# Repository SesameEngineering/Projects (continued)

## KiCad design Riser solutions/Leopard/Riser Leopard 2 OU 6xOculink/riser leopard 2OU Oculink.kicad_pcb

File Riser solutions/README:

In this folder you can find the different OCP riser solutions for both Leopard servers and Tioga Pass

For each you can find a quick summary on how to use them, electrical files (design and production files) and mechanical files for the bracket when needed

Electrical design has been done with Kicad

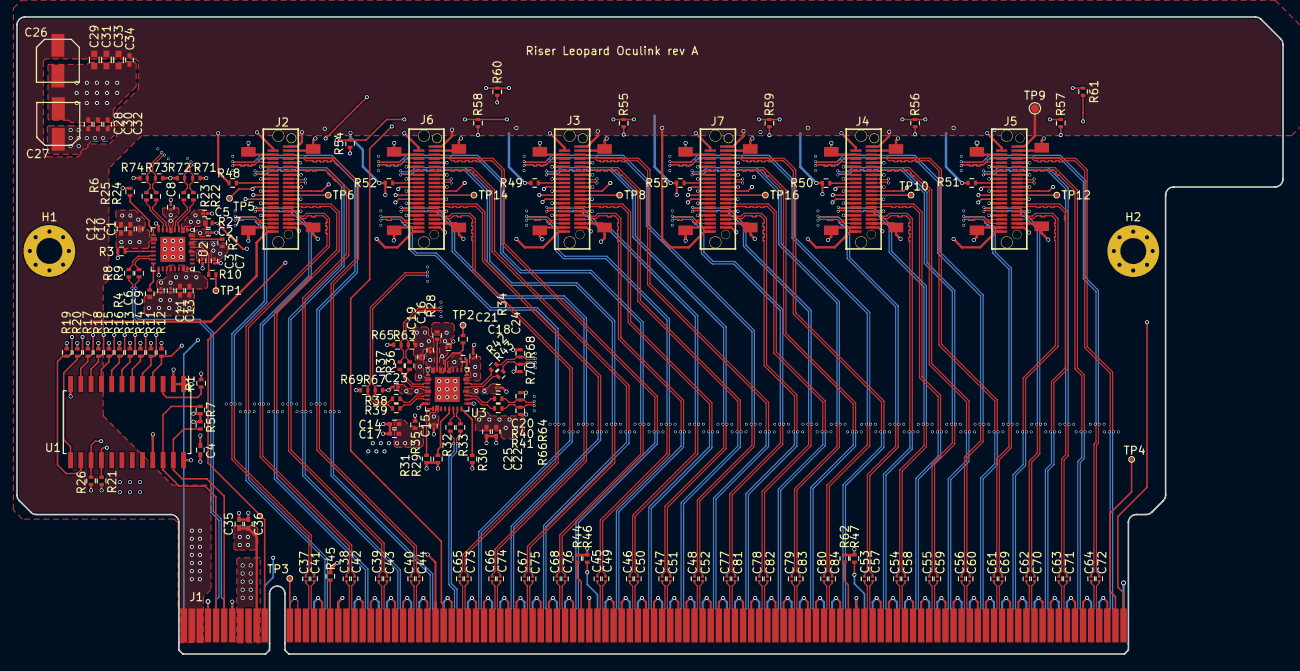
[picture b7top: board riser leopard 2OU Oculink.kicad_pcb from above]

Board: 6 copper layers, 156.4 x 78.7 mm, 183 parts (1 on the bottom side), 238 nets.

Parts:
C1, C2, C3, C5, C6, C7, C8, C9, C15, C16, C18, C19, C20, C21, C23, C24: 0.01u; C_0201
C4, C12, C13, C17, C25, C28, C30, C35: 1u 10V; C_0402
C10, C11, C14, C22: 10u 10V; C_0402
C26, C27: 100u 16V; CapaElec_100u_16V_5.3x5.3mm
C29, C31, C33: 1u 25V; C_0603
C32, C36: 0.1u 10V; C_0402
C34: 0.1u 25V; C_0402
C37, C38, C39, C40, C41, C42, C43, C44, C45, C46, C47, C48, C49, C50, C51, C52, C53, C54, C55, C56, C57, C58, C59, C60, C61, C62, C63, C64, C65, C66, C67, C68, C69, C70, C71, C72, C73, C74, C75, C76, C77, C78, C79, C80, C81, C82, C83, C84: 0.22u; C_0201
H1, H2: MountingHole_Pad; MountingHole_3.2mm_M3_Pad_Via
J1: CONN_PCIE_x24; pads_pcie_x24
J2, J3, J4, J5, J6, J7: Oculink_x4; Oculink_x4_straight_G14A42221612AHR
R1, R5, R7, R11, R12, R13, R14, R15, R16, R17, R18, R19, R20, R21, R26, R44, R45, R48, R49, R50, R51, R52, R53: 4.7k; R_0402
R2, R3, R4, R6, R28, R29, R30, R31: 2.2k; R_0402
R8, R9, R10, R22, R23, R24, R25, R27, R32, R33, R34, R35, R36, R37, R38, R39, R40, R41, R42, R43, R46, R47, R54, R55, R56, R57, R58, R59, R60, R61, R62: 0; R_0402
R63, R64, R65, R66, R67, R68, R69, R70, R71, R72, R73, R74: 49.9; R_0402
TP1, TP2: REFout; TestPoint_Pad_D0.5mm
TP3: LAN_SMB_ALERT_N; TestPoint_Pad_D0.5mm
TP4: TP1; TestPoint_Pad_D0.5mm
TP5: TP2; TestPoint_Pad_D0.5mm
TP6, TP8, TP10, TP12, TP14, TP16: BP_TYPE; TestPoint_Pad_D0.5mm
TP7: 3.3V; TestPoint_Pad_D1.0mm
TP9: 12V; TestPoint_Pad_D1.0mm
U1: PCA9548ADW; SOIC-24W_7.5x15.4mm_Pitch1.27mm
U2, U3: CLK_Buffer_4output_LMK00334RTVTQ1; WQFN-32-1EP_5x5mm_Pitch0.5mm

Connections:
+3.3VP: C5.2, C6.2, C7.2, C8.2, C9.2, C11.1, C13.1, C19.2, C20.2, C21.2, C22.1, C23.2, C24.2, C25.1, R2.2, R27.1, R28.2, R35.1, U2.2, U2.5, U2.20, U2.23, U2.30, U3.2, U3.5, U3.20, U3.23, U3.30
+3.3Vaux: C4.1, C35.1, C36.1, J1.B10, R1.2, R5.2, R7.2, R11.2, R12.2, R13.2, R14.2, R15.2, R16.2, R17.2, R18.2, R19.2, R20.2, R21.2, R26.2, U1.24
+3V3: C1.1, C2.1, C3.1, C10.1, C12.1, C14.1, C15.1, C16.1, C17.1, C18.1, C27.1, C28.1, C30.1, C32.1, J1.A9, J1.A10, J1.B8, J2.A1, J2.B21, J3.A1, J3.B21, J4.A1, J4.B21, J5.A1, J5.B21, J6.A1, J6.B21, J7.A1, J7.B21, R27.2, R35.2, R48.2, R49.2, R50.2, R51.2, R52.2, R53.2, TP7.1, U2.10, U2.28, U2.32, U3.10, U3.28, U3.32
+12V: C26.1, C29.1, C31.1, C33.1, C34.1, J1.A2, J1.A3, J1.B1, J1.B2, J1.B3, J2.A21, J2.B1, J3.A21, J3.B1, J4.A21, J4.B1, J5.A21, J5.B1, J6.A21, J6.B1, J7.A21, J7.B1, TP9.1
/CLK and I2C buffer/CLK100_R_SLOT0+: R8.2, U2.14
/CLK and I2C buffer/CLK100_R_SLOT0-: R9.2, U2.15
/CLK and I2C buffer/CLK100_R_SLOT1+: R32.2, U3.14
/CLK and I2C buffer/CLK100_R_SLOT1-: R33.2, U3.15
/CLK and I2C buffer/Oculink_0_R_CLK100+: R22.2, U2.3
/CLK and I2C buffer/Oculink_0_R_CLK100-: R23.2, U2.4
/CLK and I2C buffer/Oculink_1_R_CLK100+: R24.2, U2.6
/CLK and I2C buffer/Oculink_1_R_CLK100-: R25.2, U2.7
/CLK and I2C buffer/Oculink_2_R_CLK100+: R38.2, U3.6
/CLK and I2C buffer/Oculink_2_R_CLK100-: R39.2, U3.7
/CLK and I2C buffer/Oculink_3_R_CLK100+: R36.2, U3.3
/CLK and I2C buffer/Oculink_3_R_CLK100-: R37.2, U3.4
/CLK and I2C buffer/Oculink_4_R_CLK100+: R42.2, U3.22
/CLK and I2C buffer/Oculink_4_R_CLK100-: R43.2, U3.21
/CLK and I2C buffer/Oculink_5_R_CLK100+: R40.2, U3.19
/CLK and I2C buffer/Oculink_5_R_CLK100-: R41.2, U3.18
/Oculink connectors/Oculink_0_C_x4_TX0+: C37.2, J2.B3
/Oculink connectors/Oculink_0_C_x4_TX0-: C41.2, J2.B4
/Oculink connectors/Oculink_0_C_x4_TX1+: C38.2, J2.B6
/Oculink connectors/Oculink_0_C_x4_TX1-: C42.2, J2.B7
/Oculink connectors/Oculink_0_C_x4_TX2+: C39.2, J2.B15
/Oculink connectors/Oculink_0_C_x4_TX2-: C43.2, J2.B16
/Oculink connectors/Oculink_0_C_x4_TX3+: C40.2, J2.B18
/Oculink connectors/Oculink_0_C_x4_TX3-: C44.2, J2.B19
/Oculink connectors/Oculink_1_C_x4_TX0+: C65.2, J6.B3
/Oculink connectors/Oculink_1_C_x4_TX0-: C73.2, J6.B4
/Oculink connectors/Oculink_1_C_x4_TX1+: C66.2, J6.B6
/Oculink connectors/Oculink_1_C_x4_TX1-: C74.2, J6.B7
/Oculink connectors/Oculink_1_C_x4_TX2+: C67.2, J6.B15
/Oculink connectors/Oculink_1_C_x4_TX2-: C75.2, J6.B16
/Oculink connectors/Oculink_1_C_x4_TX3+: C68.2, J6.B18
/Oculink connectors/Oculink_1_C_x4_TX3-: C76.2, J6.B19
/Oculink connectors/Oculink_2_C_x4_TX0+: C45.2, J3.B3
/Oculink connectors/Oculink_2_C_x4_TX0-: C49.2, J3.B4
/Oculink connectors/Oculink_2_C_x4_TX1+: C46.2, J3.B6
/Oculink connectors/Oculink_2_C_x4_TX1-: C50.2, J3.B7
/Oculink connectors/Oculink_2_C_x4_TX2+: C47.2, J3.B15
/Oculink connectors/Oculink_2_C_x4_TX2-: C51.2, J3.B16
/Oculink connectors/Oculink_2_C_x4_TX3+: C48.2, J3.B18
/Oculink connectors/Oculink_2_C_x4_TX3-: C52.2, J3.B19
/Oculink connectors/Oculink_3_C_x4_TX0+: C77.2, J7.B3
/Oculink connectors/Oculink_3_C_x4_TX0-: C81.2, J7.B4
/Oculink connectors/Oculink_3_C_x4_TX1+: C78.2, J7.B6
/Oculink connectors/Oculink_3_C_x4_TX1-: C82.2, J7.B7
/Oculink connectors/Oculink_3_C_x4_TX2+: C79.2, J7.B15
/Oculink connectors/Oculink_3_C_x4_TX2-: C83.2, J7.B16
/Oculink connectors/Oculink_3_C_x4_TX3+: C80.2, J7.B18
/Oculink connectors/Oculink_3_C_x4_TX3-: C84.2, J7.B19
/Oculink connectors/Oculink_4_C_x4_TX0+: C53.2, J4.B3
/Oculink connectors/Oculink_4_C_x4_TX0-: C57.2, J4.B4
/Oculink connectors/Oculink_4_C_x4_TX1+: C54.2, J4.B6
/Oculink connectors/Oculink_4_C_x4_TX1-: C58.2, J4.B7
/Oculink connectors/Oculink_4_C_x4_TX2+: C55.2, J4.B15
/Oculink connectors/Oculink_4_C_x4_TX2-: C59.2, J4.B16
/Oculink connectors/Oculink_4_C_x4_TX3+: C56.2, J4.B18
/Oculink connectors/Oculink_4_C_x4_TX3-: C60.2, J4.B19
/Oculink connectors/Oculink_5_C_x4_TX0+: C61.2, J5.B3
/Oculink connectors/Oculink_5_C_x4_TX0-: C69.2, J5.B4
/Oculink connectors/Oculink_5_C_x4_TX1+: C62.2, J5.B6
/Oculink connectors/Oculink_5_C_x4_TX1-: C70.2, J5.B7
/Oculink connectors/Oculink_5_C_x4_TX2+: C63.2, J5.B15
/Oculink connectors/Oculink_5_C_x4_TX2-: C71.2, J5.B16
/Oculink connectors/Oculink_5_C_x4_TX3+: C64.2, J5.B18
/Oculink connectors/Oculink_5_C_x4_TX3-: C72.2, J5.B19
/PCIe x24/PCIE_SLOT0_PRSNT_x4: J1.B17, R45.2
/PCIe x24/PCIE_SLOT1_PRSNT_x1x4: J1.B48, R44.2
/PCIe x24/PRSNT1#: J1.A1, R60.1, R61.1
/PCIe x24/SLOT0_CONFIG: J1.A50, R46.2
/PCIe x24/SLOT1_CONFIG: J1.A83, R47.2
CLK100_SLOT0+: J1.A5, R8.1
CLK100_SLOT0-: J1.A6, R9.1
CLK100_SLOT1+: J1.A32, R32.1
CLK100_SLOT1-: J1.A33, R33.1
GND: C1.2, C2.2, C3.2, C4.2, C5.1, C6.1, C7.1, C8.1, C9.1, C10.2, C11.2, C12.2, C13.2, C14.2, C15.2, C16.2, C17.2, C18.2, C19.1, C20.1, C21.1, C22.2, C23.1, C24.1, C25.2, C26.2, C27.2, C28.2, C29.2, C30.2, C31.2, C32.2, C33.2, C34.2, C35.2, C36.2, H1.1, H2.1, J1.A4, J1.A7, J1.A12, J1.A15, J1.A18, J1.A20, J1.A23, J1.A24, J1.A27, J1.A28, J1.A31, J1.A34, J1.A37, J1.A38, J1.A41, J1.A42, J1.A45, J1.A46, J1.A49, J1.A51, J1.A54, J1.A55, J1.A58, J1.A59, J1.A62, J1.A63, J1.A66, J1.A67, J1.A70, J1.A71, J1.A74, J1.A75, J1.A78, J1.A79, J1.A82, J1.A84, J1.A87, J1.A88, J1.A91, J1.A92, J1.A95, J1.A96, J1.A99, J1.A100, J1.A103, J1.A104, J1.A107, J1.A108, J1.A111, J1.A112, J1.A115, J1.B4, J1.B7, J1.B13, J1.B16, J1.B18, J1.B21, J1.B22, J1.B25, J1.B26, J1.B29, J1.B30, J1.B32, J1.B35, J1.B36, J1.B39, J1.B40, J1.B43, J1.B44, J1.B47, J1.B49, J1.B52, J1.B53, J1.B56, J1.B57, J1.B60, J1.B61, J1.B64, J1.B65, J1.B68, J1.B69, J1.B72, J1.B73, J1.B76, J1.B77, J1.B80, J1.B82, J1.B85, J1.B86, J1.B89, J1.B90, J1.B93, J1.B94, J1.B97, J1.B98, J1.B101, J1.B102, J1.B105, J1.B106, J1.B109, J1.B110, J1.B113, J2.A2, J2.A5, J2.A8, J2.A11, J2.A14, J2.A17, J2.A20, J2.B2, J2.B5, J2.B8, J2.B11, J2.B14, J2.B17, J2.B20, J2.C1, J3.A2, J3.A5, J3.A8, J3.A11, J3.A14, J3.A17, J3.A20, J3.B2, J3.B5, J3.B8, J3.B11, J3.B14, J3.B17, J3.B20, J3.C1, J4.A2, J4.A5, J4.A8, J4.A11, J4.A14, J4.A17, J4.A20, J4.B2, J4.B5, J4.B8, J4.B11, J4.B14, J4.B17, J4.B20, J4.C1, J5.A2, J5.A5, J5.A8, J5.A11, J5.A14, J5.A17, J5.A20, J5.B2, J5.B5, J5.B8, J5.B11, J5.B14, J5.B17, J5.B20, J5.C1, J6.A2, J6.A5, J6.A8, J6.A11, J6.A14, J6.A17, J6.A20, J6.B2, J6.B5, J6.B8, J6.B11, J6.B14, J6.B17, J6.B20, J6.C1, J7.A2, J7.A5, J7.A8, J7.A11, J7.A14, J7.A17, J7.A20, J7.B2, J7.B5, J7.B8, J7.B11, J7.B14, J7.B17, J7.B20, J7.C1, R3.1, R4.1, R6.1, R29.1, R30.1, R31.1, R44.1, R45.1, R46.1, R47.1, R62.1, R63.1, R64.1, R65.1, R66.1, R67.1, R68.1, R69.1, R70.1, R71.1, R72.1, R73.1, R74.1, U1.1, U1.2, U1.12, U1.21, U2.1, U2.8, U2.17, U2.24, U2.33, U3.1, U3.8, U3.17, U3.24, U3.33
IRQ_LVC_WAKE_N: J1.B11, R54.2, R55.2, R56.2, R57.2, R58.2, R59.2
unnamed: J1.B12, TP3.1
unnamed: J1.B31, R60.2
unnamed: J1.B81, R62.2
unnamed: J1.B114, TP4.1
unnamed: J1.B115, R61.2
unnamed: J2.A9, TP6.1
unnamed: J2.A10, R54.1
unnamed: J2.B13, R48.1
unnamed: J3.A9, TP8.1
unnamed: J3.A10, R55.1
unnamed: J3.B13, R49.1
unnamed: J4.A9, TP10.1
unnamed: J4.A10, R56.1
unnamed: J4.B13, R50.1
unnamed: J5.A9, TP12.1
unnamed: J5.A10, R57.1
unnamed: J5.B13, R51.1
unnamed: J6.A9, TP14.1
unnamed: J6.A10, R58.1
unnamed: J6.B13, R52.1
unnamed: J7.A9, TP16.1
unnamed: J7.A10, R59.1
unnamed: J7.B13, R53.1
unnamed: R1.1, U1.3
unnamed: R2.1, U2.31
unnamed: R3.2, U2.13
unnamed: R4.2, U2.16
unnamed: R6.2, U2.9
unnamed: R10.1, TP1.1
unnamed: R10.2, U2.29
unnamed: R28.1, U3.31
unnamed: R29.2, U3.13
unnamed: R30.2, U3.16
unnamed: R31.2, U3.9
unnamed: R34.1, TP2.1
unnamed: R34.2, U3.29
Oculink_0_CLK100+: J2.A12, R22.1, R71.2
Oculink_0_CLK100-: J2.A13, R23.1, R72.2
Oculink_0_SCL: J2.B9, R19.1, U1.14
Oculink_0_SDA: J2.B10, R20.1, U1.13
Oculink_0_x4_RX0+: J1.A16, J2.A3
Oculink_0_x4_RX0-: J1.A17, J2.A4
Oculink_0_x4_RX1+: J1.A21, J2.A6
Oculink_0_x4_RX1-: J1.A22, J2.A7
Oculink_0_x4_RX2+: J1.A25, J2.A15
Oculink_0_x4_RX2-: J1.A26, J2.A16
Oculink_0_x4_RX3+: J1.A29, J2.A18
Oculink_0_x4_RX3-: J1.A30, J2.A19
Oculink_0_x4_TX0+: C37.1, J1.B14
Oculink_0_x4_TX0-: C41.1, J1.B15
Oculink_0_x4_TX1+: C38.1, J1.B19
Oculink_0_x4_TX1-: C42.1, J1.B20
Oculink_0_x4_TX2+: C39.1, J1.B23
Oculink_0_x4_TX2-: C43.1, J1.B24
Oculink_0_x4_TX3+: C40.1, J1.B27
Oculink_0_x4_TX3-: C44.1, J1.B28
Oculink_1_CLK100+: J6.A12, R24.1, R73.2
Oculink_1_CLK100-: J6.A13, R25.1, R74.2
Oculink_1_SCL: J6.B9, R11.1, U1.5
Oculink_1_SDA: J6.B10, R12.1, U1.4
Oculink_1_x4_RX0+: J1.A35, J6.A3
Oculink_1_x4_RX0-: J1.A36, J6.A4
Oculink_1_x4_RX1+: J1.A39, J6.A6
Oculink_1_x4_RX1-: J1.A40, J6.A7
Oculink_1_x4_RX2+: J1.A43, J6.A15
Oculink_1_x4_RX2-: J1.A44, J6.A16
Oculink_1_x4_RX3+: J1.A47, J6.A18
Oculink_1_x4_RX3-: J1.A48, J6.A19
Oculink_1_x4_TX0+: C65.1, J1.B33
Oculink_1_x4_TX0-: C73.1, J1.B34
Oculink_1_x4_TX1+: C66.1, J1.B37
Oculink_1_x4_TX1-: C74.1, J1.B38
Oculink_1_x4_TX2+: C67.1, J1.B41
Oculink_1_x4_TX2-: C75.1, J1.B42
Oculink_1_x4_TX3+: C68.1, J1.B45
Oculink_1_x4_TX3-: C76.1, J1.B46
Oculink_2_CLK100+: J3.A12, R38.1, R67.2
Oculink_2_CLK100-: J3.A13, R39.1, R69.2
Oculink_2_SCL: J3.B9, R13.1, U1.7
Oculink_2_SDA: J3.B10, R14.1, U1.6
Oculink_2_x4_RX0+: J1.A52, J3.A3
Oculink_2_x4_RX0-: J1.A53, J3.A4
Oculink_2_x4_RX1+: J1.A56, J3.A6
Oculink_2_x4_RX1-: J1.A57, J3.A7
Oculink_2_x4_RX2+: J1.A60, J3.A15
Oculink_2_x4_RX2-: J1.A61, J3.A16
Oculink_2_x4_RX3+: J1.A64, J3.A18
Oculink_2_x4_RX3-: J1.A65, J3.A19
Oculink_2_x4_TX0+: C45.1, J1.B50
Oculink_2_x4_TX0-: C49.1, J1.B51
Oculink_2_x4_TX1+: C46.1, J1.B54
Oculink_2_x4_TX1-: C50.1, J1.B55
Oculink_2_x4_TX2+: C47.1, J1.B58
Oculink_2_x4_TX2-: C51.1, J1.B59
Oculink_2_x4_TX3+: C48.1, J1.B62
Oculink_2_x4_TX3-: C52.1, J1.B63
Oculink_3_CLK100+: J7.A12, R36.1, R63.2
Oculink_3_CLK100-: J7.A13, R37.1, R65.2
Oculink_3_SCL: J7.B9, R15.1, U1.9
Oculink_3_SDA: J7.B10, R16.1, U1.8
Oculink_3_x4_RX0+: J1.A68, J7.A3
Oculink_3_x4_RX0-: J1.A69, J7.A4
Oculink_3_x4_RX1+: J1.A72, J7.A6
Oculink_3_x4_RX1-: J1.A73, J7.A7
Oculink_3_x4_RX2+: J1.A76, J7.A15
Oculink_3_x4_RX2-: J1.A77, J7.A16
Oculink_3_x4_RX3+: J1.A80, J7.A18
Oculink_3_x4_RX3-: J1.A81, J7.A19
Oculink_3_x4_TX0+: C77.1, J1.B66
Oculink_3_x4_TX0-: C81.1, J1.B67
Oculink_3_x4_TX1+: C78.1, J1.B70
Oculink_3_x4_TX1-: C82.1, J1.B71
Oculink_3_x4_TX2+: C79.1, J1.B74
Oculink_3_x4_TX2-: C83.1, J1.B75
Oculink_3_x4_TX3+: C80.1, J1.B78
Oculink_3_x4_TX3-: C84.1, J1.B79
Oculink_4_CLK100+: J4.A12, R42.1, R68.2
Oculink_4_CLK100-: J4.A13, R43.1, R70.2
Oculink_4_SCL: J4.B9, R17.1, U1.11
Oculink_4_SDA: J4.B10, R18.1, U1.10
Oculink_4_x4_RX0+: J1.A85, J4.A3
Oculink_4_x4_RX0-: J1.A86, J4.A4
Oculink_4_x4_RX1+: J1.A89, J4.A6
Oculink_4_x4_RX1-: J1.A90, J4.A7
Oculink_4_x4_RX2+: J1.A93, J4.A15
Oculink_4_x4_RX2-: J1.A94, J4.A16
Oculink_4_x4_RX3+: J1.A97, J4.A18
Oculink_4_x4_RX3-: J1.A98, J4.A19
Oculink_4_x4_TX0+: C53.1, J1.B83
Oculink_4_x4_TX0-: C57.1, J1.B84
Oculink_4_x4_TX1+: C54.1, J1.B87
Oculink_4_x4_TX1-: C58.1, J1.B88
Oculink_4_x4_TX2+: C55.1, J1.B91
Oculink_4_x4_TX2-: C59.1, J1.B92
Oculink_4_x4_TX3+: C56.1, J1.B95
Oculink_4_x4_TX3-: C60.1, J1.B96
Oculink_5_CLK100+: J5.A12, R40.1, R64.2
Oculink_5_CLK100-: J5.A13, R41.1, R66.2
Oculink_5_SCL: J5.B9, R21.1, U1.16
Oculink_5_SDA: J5.B10, R26.1, U1.15
Oculink_5_x4_RX0+: J1.A101, J5.A3
Oculink_5_x4_RX0-: J1.A102, J5.A4
Oculink_5_x4_RX1+: J1.A105, J5.A6
Oculink_5_x4_RX1-: J1.A106, J5.A7
Oculink_5_x4_RX2+: J1.A109, J5.A15
Oculink_5_x4_RX2-: J1.A110, J5.A16
Oculink_5_x4_RX3+: J1.A113, J5.A18
Oculink_5_x4_RX3-: J1.A114, J5.A19
Oculink_5_x4_TX0+: C61.1, J1.B99
Oculink_5_x4_TX0-: C69.1, J1.B100
Oculink_5_x4_TX1+: C62.1, J1.B103
Oculink_5_x4_TX1-: C70.1, J1.B104
Oculink_5_x4_TX2+: C63.1, J1.B107
Oculink_5_x4_TX2-: C71.1, J1.B108
Oculink_5_x4_TX3+: C64.1, J1.B111
Oculink_5_x4_TX3-: C72.1, J1.B112
RST_PERST0_N: J1.A11, J2.B12, J3.B12, J4.B12, J5.B12, J6.B12, J7.B12, TP5.1
SMB_CLK: J1.B5, R7.1, U1.22
SMB_DATA: J1.B6, R5.1, U1.23

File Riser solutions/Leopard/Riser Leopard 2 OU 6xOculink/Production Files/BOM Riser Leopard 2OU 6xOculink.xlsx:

Id | Reference | Footprint | Quantity | Designation | Manufacturer | Manufacturer part number
1 | R30,R2,R3,R4,R6,R28,R29,R31 | R_0402 | 8 | 2.2k | ROHM Semiconductor | SFR01MZPF2201
2 | C1,C2,C3,C5,C6,C7,C8,C9,C15,C16,C18,C19,C20,C21,C23,C24 | C_0201 | 16 | 0.01u | Murata Electronics | GRM033R71A103KA01D
3 | C4,C12,C13,C17,C25,C28,C30,C35 | C_0402 | 8 | 1u 10V | Taiyo Yuden | LMK105BJ105MVHF
4 | C10,C11,C14,C22 | C_0402 | 4 | 10u 10V | Samsung Electro-Mechanics | CL05A106MP5NUNC
5 | C29,C31,C33 | C_0603 | 3 | 1u 25V | Taiyo Yuden | TMK107B7105KA-T
6 | C32,C36 | C_0402 | 2 | 0.1u 10V | Taiyo Yuden | LMF105B7104MVHF
7 | C34 | C_0402 | 1 | 0.1u 25V | Taiyo Yuden | TMK105B7104MV-FR
8 | C37,C38,C39,C40,C41,C42,C43,C44,C45,C46,C47,C48,C49,C50,C51,C52,C53,C54,C55,C56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 | C_0201 | 48 | 0.22u | Murata Electronics | GRM033R61C224KE14J
9 | R1,R5,R7,R11,R12,R13,R14,R15,R16,R17,R18,R19,R20,R21,R26,R44,R45,R48,R49,R50,R5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 | R_0402 | 23 | 4.7k | ROHM Semiconductor | SFR01MZPF4701
10 | R8,R9,R10,R22,R23,R24,R25,R27,R32,R33,R34,R35,R36,R37,R38,R39,R40,R41,R42,R43,R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 | R_0402 | 31 | 0 | Bourns | CR0402-J/-000GLF
11 | U2,U3 | WQFN-32-1EP_5x5mm_Pitch0.5mm | 2 | CLK_Buffer_4output_LMK00334RTVTQ1 | Texas Instruments | LMK00334RTVTQ1
12 | C26,C27 | CapaElec_100u_16V_5.3x5.3mm | 2 | 100u 16V | Panasonic | EEE-FN1C101UR
13 | U1 | SOIC-24W_7.5x15.4mm_Pitch1.27mm | 1 | PCA9548ADW | Texas Instruments | PCA9548ADW
14 | J4,J3,J7,J2,J6,J5 | Oculink_x4_straight_G14A42221612AHR | 6 | Oculink_x4 | Amphenol Commercial Products | G14A42221612AHR
15 | R63,R64,R65,R66,R67,R68,R69,R70,R71,R72,R73,R74 | R_0402 | 12 | 49.9 | ROHM Semiconductor | SFR01MZPF49R9

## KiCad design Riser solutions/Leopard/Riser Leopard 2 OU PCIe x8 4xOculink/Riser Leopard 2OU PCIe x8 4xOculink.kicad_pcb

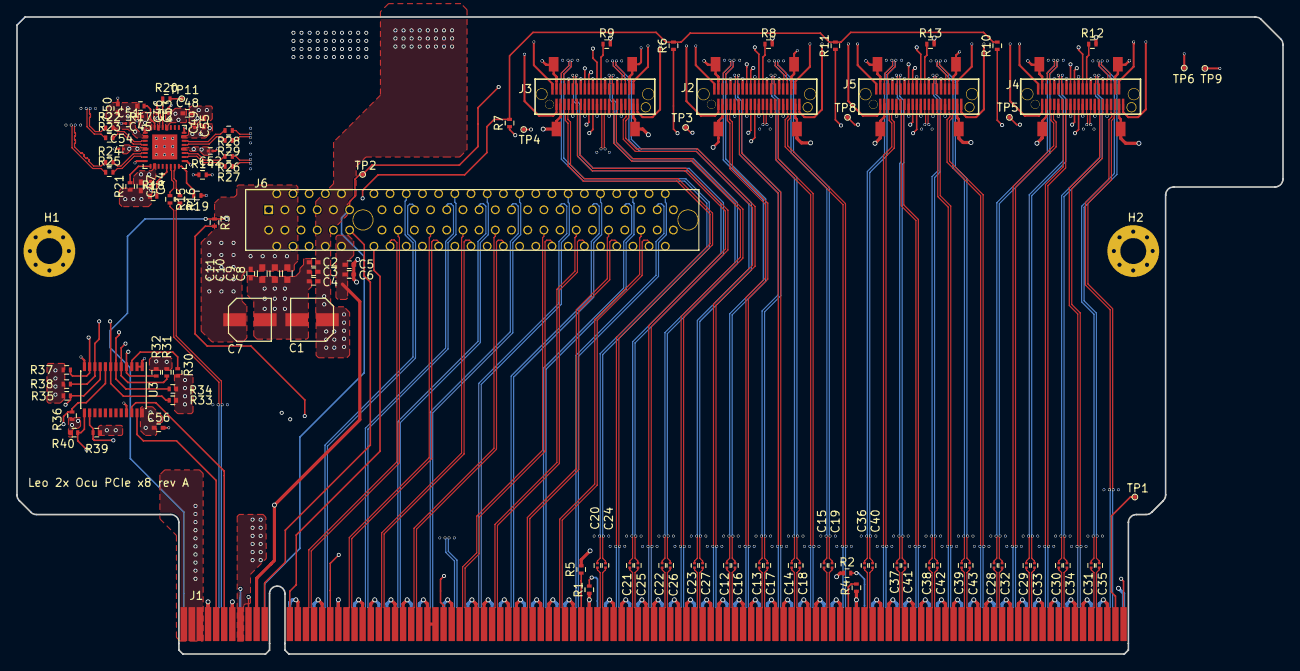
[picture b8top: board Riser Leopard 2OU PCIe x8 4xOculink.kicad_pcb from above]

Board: 6 copper layers, 156.4 x 78.7 mm, 115 parts (0 on the bottom side), 200 nets.

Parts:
C1, C7: 100u 16V; CapaElec_100u_16V_5.3x5.3mm
C2, C3, C5, C48, C50, C56: 1u 10V; C_0402
C4, C6: 0.1u 10V; C_0402
C8, C9, C10: 1u 25V; C_0603
C11: 0.1u 25V; C_0402
C12, C13, C14, C15, C16, C17, C18, C19, C20, C21, C22, C23, C24, C25, C26, C27, C28, C29, C30, C31, C32, C33, C34, C35, C36, C37, C38, C39, C40, C41, C42, C43: 0.22u; C_0201
C44, C45, C46, C51, C52, C53, C54, C55: 0.01u; C_0201
C47, C49: 10u 10V; C_0402
H1, H2: MountingHole_Pad; MountingHole_3.2mm_M3_Pad_Via
J1: CONN_PCIE_x24; pads_pcie_x24
J2, J3, J4, J5: Oculink_x4; Oculink_x4_straight_G14A42221612AHR
J6: connector_pcie8x; pcie_8x_straight
R1, R2, R3, R4, R6, R7, R10, R11, R14, R15, R16, R20, R22, R23, R24, R25, R26, R27, R28, R29: 0; R_0402
R5, R8, R9, R12, R13, R30, R31, R32, R33, R34, R35, R36, R37, R38, R39, R40: 4.7k; R_0402
R17, R18, R19, R21: 2.2k; R_0402
TP1: TP1; TestPoint_Pad_D0.5mm
TP2: TP2; TestPoint_Pad_D0.5mm
TP3, TP4, TP5, TP8: BP_TYPE; TestPoint_Pad_D0.5mm
TP6: 3.3V; TestPoint_Pad_D0.5mm
TP9: 12V; TestPoint_Pad_D0.5mm
TP11: TestPoint; TestPoint_Pad_D0.5mm
U2: CLK_Buffer_4output_LMK00334RTVRQ1; WQFN-32-1EP_5x5mm_Pitch0.5mm
U3: PCA9548APW,118; TSSOP-24_4.4x7.8mm_Pitch0.65mm

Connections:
+3.3VP: C49.1, C50.1, C51.2, C52.2, C53.2, C54.2, C55.2, R14.1, R17.2, U2.2, U2.5, U2.20, U2.23, U2.30
+3.3Vaux: C5.1, C6.1, C56.1, J1.B10, J6.B10, R30.2, R31.2, R32.1, R33.2, R34.1, R35.2, R36.1, R37.2, R38.1, R39.2, R40.1, U3.24
+3V3: C1.1, C2.1, C3.1, C4.1, C44.1, C45.1, C46.1, C47.1, C48.1, J1.A9, J1.A10, J1.B8, J2.A1, J2.B21, J3.A1, J3.B21, J4.A1, J4.B21, J5.A1, J5.B21, J6.A9, J6.A10, J6.B8, R8.2, R9.2, R12.2, R13.2, R14.2, TP6.1, U2.10, U2.28, U2.32
+12V: C7.1, C8.1, C9.1, C10.1, C11.1, J1.A2, J1.A3, J1.B1, J1.B2, J1.B3, J2.A21, J2.B1, J3.A21, J3.B1, J4.A21, J4.B1, J5.A21, J5.B1, J6.A2, J6.A3, J6.B1, J6.B2, J6.B3, TP9.1
/CLK and I2C buffer/CLK100_R_SLOT0+: R15.1, U2.14
/CLK and I2C buffer/CLK100_R_SLOT0-: R16.1, U2.15
/CLK and I2C buffer/Oculink_0_R_CLK100+: R22.2, U2.3
/CLK and I2C buffer/Oculink_0_R_CLK100-: R23.2, U2.4
/CLK and I2C buffer/Oculink_1_R_CLK100+: R24.2, U2.6
/CLK and I2C buffer/Oculink_1_R_CLK100-: R25.2, U2.7
/CLK and I2C buffer/Oculink_2_R_CLK100+: R28.2, U2.22
/CLK and I2C buffer/Oculink_2_R_CLK100-: R29.2, U2.21
/CLK and I2C buffer/Oculink_3_R_CLK100+: R26.2, U2.19
/CLK and I2C buffer/Oculink_3_R_CLK100-: R27.2, U2.18
/CPU0_RX0+: J1.A16, J6.A16
/CPU0_RX0-: J1.A17, J6.A17
/CPU0_RX1+: J1.A21, J6.A21
/CPU0_RX1-: J1.A22, J6.A22
/CPU0_RX2+: J1.A25, J6.A25
/CPU0_RX2-: J1.A26, J6.A26
/CPU0_RX3+: J1.A29, J6.A29
/CPU0_RX3-: J1.A30, J6.A30
/CPU0_RX4+: J1.A35, J6.A35
/CPU0_RX4-: J1.A36, J6.A36
/CPU0_RX5+: J1.A39, J6.A39
/CPU0_RX5-: J1.A40, J6.A40
/CPU0_RX6+: J1.A43, J6.A43
/CPU0_RX6-: J1.A44, J6.A44
/CPU0_RX7+: J1.A47, J6.A47
/CPU0_RX7-: J1.A48, J6.A48
/CPU0_TX0+: J1.B14, J6.B14
/CPU0_TX0-: J1.B15, J6.B15
/CPU0_TX1+: J1.B19, J6.B19
/CPU0_TX1-: J1.B20, J6.B20
/CPU0_TX2+: J1.B23, J6.B23
/CPU0_TX2-: J1.B24, J6.B24
/CPU0_TX3+: J1.B27, J6.B27
/CPU0_TX3-: J1.B28, J6.B28
/CPU0_TX4+: J1.B33, J6.B33
/CPU0_TX4-: J1.B34, J6.B34
/CPU0_TX5+: J1.B37, J6.B37
/CPU0_TX5-: J1.B38, J6.B38
/CPU0_TX6+: J1.B41, J6.B41
/CPU0_TX6-: J1.B42, J6.B42
/CPU0_TX7+: J1.B45, J6.B45
/CPU0_TX7-: J1.B46, J6.B46
/LAN_SMB_ALERT_N: J1.B12, J6.B12
/LAN_SMB_CLK: J1.B9, J6.A32
/LAN_SMB_DAT: J1.A8, J6.A33
/Oculink connector/Oculink_0_C_x4_TX0+: C20.2, J3.B3
/Oculink connector/Oculink_0_C_x4_TX0-: C24.2, J3.B4
/Oculink connector/Oculink_0_C_x4_TX1+: C21.2, J3.B6
/Oculink connector/Oculink_0_C_x4_TX1-: C25.2, J3.B7
/Oculink connector/Oculink_0_C_x4_TX2+: C22.2, J3.B15
/Oculink connector/Oculink_0_C_x4_TX2-: C26.2, J3.B16
/Oculink connector/Oculink_0_C_x4_TX3+: C23.2, J3.B18
/Oculink connector/Oculink_0_C_x4_TX3-: C27.2, J3.B19
/Oculink connector/Oculink_1_C_x4_TX0+: C12.2, J2.B3
/Oculink connector/Oculink_1_C_x4_TX0-: C16.2, J2.B4
/Oculink connector/Oculink_1_C_x4_TX1+: C13.2, J2.B6
/Oculink connector/Oculink_1_C_x4_TX1-: C17.2, J2.B7
/Oculink connector/Oculink_1_C_x4_TX2+: C14.2, J2.B15
/Oculink connector/Oculink_1_C_x4_TX2-: C18.2, J2.B16
/Oculink connector/Oculink_1_C_x4_TX3+: C15.2, J2.B18
/Oculink connector/Oculink_1_C_x4_TX3-: C19.2, J2.B19
/Oculink connector/Oculink_2_C_x4_TX0+: C36.2, J5.B3
/Oculink connector/Oculink_2_C_x4_TX0-: C40.2, J5.B4
/Oculink connector/Oculink_2_C_x4_TX1+: C37.2, J5.B6
/Oculink connector/Oculink_2_C_x4_TX1-: C41.2, J5.B7
/Oculink connector/Oculink_2_C_x4_TX2+: C38.2, J5.B15
/Oculink connector/Oculink_2_C_x4_TX2-: C42.2, J5.B16
/Oculink connector/Oculink_2_C_x4_TX3+: C39.2, J5.B18
/Oculink connector/Oculink_2_C_x4_TX3-: C43.2, J5.B19
/Oculink connector/Oculink_3_C_x4_TX0+: C28.2, J4.B3
/Oculink connector/Oculink_3_C_x4_TX0-: C32.2, J4.B4
/Oculink connector/Oculink_3_C_x4_TX1+: C29.2, J4.B6
/Oculink connector/Oculink_3_C_x4_TX1-: C33.2, J4.B7
/Oculink connector/Oculink_3_C_x4_TX2+: C30.2, J4.B15
/Oculink connector/Oculink_3_C_x4_TX2-: C34.2, J4.B16
/Oculink connector/Oculink_3_C_x4_TX3+: C31.2, J4.B18
/Oculink connector/Oculink_3_C_x4_TX3-: C35.2, J4.B19
/PCIE_SLOT0_PRSNT_x4: J1.B17, J6.B17, J6.B31
/PCIE_SLOT0_PRSNT_x8: J1.B31, J6.B48
/PCIE_SLOT1_PRSNT_x1x4: J1.B48, R5.1
/PCIE_SLOT_PRSNT#1: J1.A1, J6.A1, R3.1
/SLOT0_CONFIG: J1.A50, R1.2
/SLOT1_CONFIG: J1.A83, R2.2
CLK100_SLOT0+: J1.A5, R15.2
CLK100_SLOT0-: J1.A6, R16.2
CLK100_SLOT1+: J1.A32, J6.A13
CLK100_SLOT1-: J1.A33, J6.A14
GND: C1.2, C2.2, C3.2, C4.2, C5.2, C6.2, C7.2, C8.2, C9.2, C10.2, C11.2, C44.2, C45.2, C46.2, C47.2, C48.2, C49.2, C50.2, C51.1, C52.1, C53.1, C54.1, C55.1, C56.2, H1.1, H2.1, J1.A4, J1.A7, J1.A12, J1.A15, J1.A18, J1.A20, J1.A23, J1.A24, J1.A27, J1.A28, J1.A31, J1.A34, J1.A37, J1.A38, J1.A41, J1.A42, J1.A45, J1.A46, J1.A49, J1.A51, J1.A54, J1.A55, J1.A58, J1.A59, J1.A62, J1.A63, J1.A66, J1.A67, J1.A70, J1.A71, J1.A74, J1.A75, J1.A78, J1.A79, J1.A82, J1.A84, J1.A87, J1.A88, J1.A91, J1.A92, J1.A95, J1.A96, J1.A99, J1.A100, J1.A103, J1.A104, J1.A107, J1.A108, J1.A111, J1.A112, J1.A115, J1.B4, J1.B7, J1.B13, J1.B16, J1.B18, J1.B21, J1.B22, J1.B25, J1.B26, J1.B29, J1.B30, J1.B32, J1.B35, J1.B36, J1.B39, J1.B40, J1.B43, J1.B44, J1.B47, J1.B49, J1.B52, J1.B53, J1.B56, J1.B57, J1.B60, J1.B61, J1.B64, J1.B65, J1.B68, J1.B69, J1.B72, J1.B73, J1.B76, J1.B77, J1.B80, J1.B82, J1.B85, J1.B86, J1.B89, J1.B90, J1.B93, J1.B94, J1.B97, J1.B98, J1.B101, J1.B102, J1.B105, J1.B106, J1.B109, J1.B110, J1.B113, J2.A2, J2.A5, J2.A8, J2.A11, J2.A14, J2.A17, J2.A20, J2.B2, J2.B5, J2.B8, J2.B11, J2.B14, J2.B17, J2.B20, J2.C1, J3.A2, J3.A5, J3.A8, J3.A11, J3.A14, J3.A17, J3.A20, J3.B2, J3.B5, J3.B8, J3.B11, J3.B14, J3.B17, J3.B20, J3.C1, J4.A2, J4.A5, J4.A8, J4.A11, J4.A14, J4.A17, J4.A20, J4.B2, J4.B5, J4.B8, J4.B11, J4.B14, J4.B17, J4.B20, J4.C1, J5.A2, J5.A5, J5.A8, J5.A11, J5.A14, J5.A17, J5.A20, J5.B2, J5.B5, J5.B8, J5.B11, J5.B14, J5.B17, J5.B20, J5.C1, J6.A4, J6.A12, J6.A15, J6.A18, J6.A20, J6.A23, J6.A24, J6.A27, J6.A28, J6.A31, J6.A34, J6.A37, J6.A38, J6.A41, J6.A42, J6.A45, J6.A46, J6.A49, J6.B4, J6.B7, J6.B13, J6.B16, J6.B18, J6.B21, J6.B22, J6.B25, J6.B26, J6.B29, J6.B32, J6.B35, J6.B36, J6.B39, J6.B40, J6.B43, J6.B44, J6.B47, J6.B49, R1.1, R2.1, R4.1, R5.2, R18.1, R19.1, R21.1, U2.1, U2.8, U2.17, U2.24, U2.33, U3.1, U3.2, U3.12, U3.21
IRQ_LVC_WAKE_N: J1.B11, J6.B11, R6.2, R7.2, R10.2, R11.2
unnamed: J1.B81, R4.2
unnamed: J1.B114, TP1.1
unnamed: J1.B115, R3.2
unnamed: J2.A9, TP3.1
unnamed: J2.A10, R6.1
unnamed: J2.B13, R8.1
unnamed: J3.A9, TP4.1
unnamed: J3.A10, R7.1
unnamed: J3.B13, R9.1
unnamed: J4.A9, TP5.1
unnamed: J4.A10, R10.1
unnamed: J4.B13, R12.1
unnamed: J5.A9, TP8.1
unnamed: J5.A10, R11.1
unnamed: J5.B13, R13.1
unnamed: R17.1, U2.31
unnamed: R18.2, U2.13
unnamed: R19.2, U2.16
unnamed: R20.1, U2.29
unnamed: R20.2, TP11.1
unnamed: R21.2, U2.9
unnamed: R30.1, U3.3
Oculink_0_CLK100+: J3.A12, R22.1
Oculink_0_CLK100-: J3.A13, R23.1
Oculink_0_SMB_CLK: J3.B9, R37.1, U3.11
Oculink_0_SMB_DATA: J3.B10, R38.2, U3.10
Oculink_0_x4_RX0+: J1.A52, J3.A3
Oculink_0_x4_RX0-: J1.A53, J3.A4
Oculink_0_x4_RX1+: J1.A56, J3.A6
Oculink_0_x4_RX1-: J1.A57, J3.A7
Oculink_0_x4_RX2+: J1.A60, J3.A15
Oculink_0_x4_RX2-: J1.A61, J3.A16
Oculink_0_x4_RX3+: J1.A64, J3.A18
Oculink_0_x4_RX3-: J1.A65, J3.A19
Oculink_0_x4_TX0+: C20.1, J1.B50
Oculink_0_x4_TX0-: C24.1, J1.B51
Oculink_0_x4_TX1+: C21.1, J1.B54
Oculink_0_x4_TX1-: C25.1, J1.B55
Oculink_0_x4_TX2+: C22.1, J1.B58
Oculink_0_x4_TX2-: C26.1, J1.B59
Oculink_0_x4_TX3+: C23.1, J1.B62
Oculink_0_x4_TX3-: C27.1, J1.B63
Oculink_1_CLK100+: J2.A12, R24.1
Oculink_1_CLK100-: J2.A13, R25.1
Oculink_1_SMB_CLK: J2.B9, R33.1, U3.7
Oculink_1_SMB_DATA: J2.B10, R34.2, U3.6
Oculink_1_x4_RX0+: J1.A68, J2.A3
Oculink_1_x4_RX0-: J1.A69, J2.A4
Oculink_1_x4_RX1+: J1.A72, J2.A6
Oculink_1_x4_RX1-: J1.A73, J2.A7
Oculink_1_x4_RX2+: J1.A76, J2.A15
Oculink_1_x4_RX2-: J1.A77, J2.A16
Oculink_1_x4_RX3+: J1.A80, J2.A18
Oculink_1_x4_RX3-: J1.A81, J2.A19
Oculink_1_x4_TX0+: C12.1, J1.B66
Oculink_1_x4_TX0-: C16.1, J1.B67
Oculink_1_x4_TX1+: C13.1, J1.B70
Oculink_1_x4_TX1-: C17.1, J1.B71
Oculink_1_x4_TX2+: C14.1, J1.B74
Oculink_1_x4_TX2-: C18.1, J1.B75
Oculink_1_x4_TX3+: C15.1, J1.B78
Oculink_1_x4_TX3-: C19.1, J1.B79
Oculink_2_CLK100+: J5.A12, R28.1
Oculink_2_CLK100-: J5.A13, R29.1
Oculink_2_SMB_CLK: J5.B9, R39.1, U3.14
Oculink_2_SMB_DATA: J5.B10, R40.2, U3.13
Oculink_2_x4_RX0+: J1.A85, J5.A3
Oculink_2_x4_RX0-: J1.A86, J5.A4
Oculink_2_x4_RX1+: J1.A89, J5.A6
Oculink_2_x4_RX1-: J1.A90, J5.A7
Oculink_2_x4_RX2+: J1.A93, J5.A15
Oculink_2_x4_RX2-: J1.A94, J5.A16
Oculink_2_x4_RX3+: J1.A97, J5.A18
Oculink_2_x4_RX3-: J1.A98, J5.A19
Oculink_2_x4_TX0+: C36.1, J1.B83
Oculink_2_x4_TX0-: C40.1, J1.B84
Oculink_2_x4_TX1+: C37.1, J1.B87
Oculink_2_x4_TX1-: C41.1, J1.B88
Oculink_2_x4_TX2+: C38.1, J1.B91
Oculink_2_x4_TX2-: C42.1, J1.B92
Oculink_2_x4_TX3+: C39.1, J1.B95
Oculink_2_x4_TX3-: C43.1, J1.B96
Oculink_3_CLK100+: J4.A12, R26.1
Oculink_3_CLK100-: J4.A13, R27.1
Oculink_3_SMB_CLK: J4.B9, R35.1, U3.9
Oculink_3_SMB_DATA: J4.B10, R36.2, U3.8
Oculink_3_x4_RX0+: J1.A101, J4.A3
Oculink_3_x4_RX0-: J1.A102, J4.A4
Oculink_3_x4_RX1+: J1.A105, J4.A6
Oculink_3_x4_RX1-: J1.A106, J4.A7
Oculink_3_x4_RX2+: J1.A109, J4.A15
Oculink_3_x4_RX2-: J1.A110, J4.A16
Oculink_3_x4_RX3+: J1.A113, J4.A18
Oculink_3_x4_RX3-: J1.A114, J4.A19
Oculink_3_x4_TX0+: C28.1, J1.B99
Oculink_3_x4_TX0-: C32.1, J1.B100
Oculink_3_x4_TX1+: C29.1, J1.B103
Oculink_3_x4_TX1-: C33.1, J1.B104
Oculink_3_x4_TX2+: C30.1, J1.B107
Oculink_3_x4_TX2-: C34.1, J1.B108
Oculink_3_x4_TX3+: C31.1, J1.B111
Oculink_3_x4_TX3-: C35.1, J1.B112
PCIe_SMB_CLK: J6.B5, R31.1, U3.5
PCIe_SMB_DATA: J6.B6, R32.2, U3.4
RST_PERST0_N: J1.A11, J2.B12, J3.B12, J4.B12, J5.B12, J6.A11, TP2.1
SMB_CLK: J1.B5, U3.23
SMB_DATA: J1.B6, U3.22

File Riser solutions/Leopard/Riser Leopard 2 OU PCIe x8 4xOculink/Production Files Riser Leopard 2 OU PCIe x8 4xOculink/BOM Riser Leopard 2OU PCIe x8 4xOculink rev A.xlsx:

Id | Reference | Footprint | Quantity | Designation | Manufacturer | Manufacturer part number
1 | R34,R5,R8,R9,R12,R13,R30,R31,R32,R33,R35,R36,R37,R38,R39,R40 | R_0402 | 16 | 4.7k | ROHM Semiconductor | SFR01MZPF4701
4 | C1,C7 | CapaElec_100u_16V_5.3x5.3mm | 2 | 100u 16V | Panasonic | EEEFK1C101SR
5 | C2,C3,C5,C48,C50,C56 | C_0402 | 6 | 1u 10V | Taiyo Yuden | LMK105BJ105MVHF
6 | C4,C6 | C_0402 | 2 | 0.1u 10V | Taiyo Yuden | LMF105B7104MVHF
7 | C8,C9,C10 | C_0603 | 3 | 1u 25V | Taiyo Yuden | TMK107B7105KA-T
8 | C11 | C_0402 | 1 | 0.1u 25V | Taiyo Yuden | TMK105B7104MV-FR
9 | C12,C13,C14,C15,C16,C17,C18,C19,C20,C21,C22,C23,C24,C25,C26,C27,C28,C29,C30,C31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 | C_0201 | 32 | 0.22u | Murata Electronics | GRM033R61C224KE14J
10 | C44,C45,C46,C51,C52,C53,C54,C55 | C_0201 | 8 | 0.01u | Murata Electronics | GRM033R71A103KA01D
11 | C47,C49 | C_0402 | 2 | 10u 10V | Samsung Electro-Mechanics | CL05A106MP5NUNC
12 | J2,J3,J4,J5 | Oculink_x4_straight_G14A42221612AHR | 4 | Oculink_x4 | Amphenol Commercial Products | G14A42221612AHR
13 | R1,R2,R3,R4,R6,R7,R10,R11,R14,R15,R16,R20,R22,R23,R24,R25,R26,R27,R28,R29 | R_0402 | 20 | 0 | Bourns | CR0402-J/-000GLF
14 | R17,R18,R19,R21 | R_0402 | 4 | 2.2k | ROHM Semiconductor | SFR01MZPF2201
21 | U2 | WQFN-32-1EP_5x5mm_Pitch0.5mm | 1 | CLK_Buffer_4output_LMK00334RTVRQ1 | Texas Instruments | LMK00334RTVRQ1
22 | U3 | TSSOP-24_4.4x7.8mm_Pitch0.65mm | 1 | PCA9548APW,118 | Texas Instruments | PCA9548APW,118
23 | J6 | pcie_8x_straight | 1 | connector_pcie8x | Amphenol FCI | 10018783-10002MLF

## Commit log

2022-02-16 Create test
2022-02-17 Create readme.md
    Thermal simulation report for mechanical design
2022-02-17 Rename Readme.md to README.md
2022-03-03 Create README.md
    Mechanical files for 1U slot
2022-03-03 Create README.md
    Mechanical files redundant discovery
2022-03-03 Create 1U slot for switch
2022-03-03 Create README.md
    This folder contains the CAD of the discovery chassis
2022-03-03 Create README.md
    This folder contains all the CAD and drawing for the ORV2 to EIA rack adaptor kit.
    This kit is design to integrate Leopard and Tigapass servers in a Standard 19 in rack, powered by a busbar and ORV1 stingray powershelf.
2022-03-03 Create README.md
    Mechanical CAD files
